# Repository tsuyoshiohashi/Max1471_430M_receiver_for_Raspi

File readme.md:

# MAX1471＋AD5700 430MHz AFSK receiver for Raspi

Receive 1200bps AFSK modulated waves in the 430Mhz band with RaspberryPi and an expansion board (MAX1471 + AD5700 430M radio hat, home made, see hat directory).
(In the photo, the LC series trap is directly attached to the U4 pin, but it has been modified in the circuit diagram.)

・The receiving frequency is fixed at the frequency determined by the XTAL frequency.

-Confirmed reception of a 1200bps AFSK signal in Asynchronous format (UART) sent by Gnuradio+Pluto. 

Please refer to the gnuradio directory for the transmitting program.

# Environment where operation has been confirmed
Raspi3B+　Raspberry Pi OS(bookworm)

You need to install pigpio.

# HAT configuration and operation
I use Analog Devices' MAX1471 for reception and AD5700 for AFSK demodulation.

MAX1471 operates in Continuous Receive Mode.

## receiving data
The received data RXD is connected to GPIO15 (pin10) of Raspi, and if the received data is in UART format, it can be treated as /dev/ttyAMA0 by setting UART on Raspi, and it can be displayed on minicom.
(Device name may vary depending on Raspino model)

`Example) $ cat /dev/ttyAMA0`

`Example) $ minicom -b 1200 -D /dev/ttyAMA0`

Since there is no squelch, the data becomes meaningless when there is no signal.

You can determine whether there is a received signal by looking at the CD signal of the AD5700 or by the size of the RSSI signal.

Please refer to rxafsk.py.

## receiving frequency
The receiving frequency is determined by the Xtal frequency using the following formula.
$$ frx = (fxtal * 32) + 10.7 (MHz) $$

13.2256MHz becomes 433.920MHz.

Although the data sheet says, the sensitivity is higher at frequencies slightly lower than this.
The prototype board had better sensitivity at frequencies several tens of KHz lower.

If you want to change the receiving frequency, you must also change the value of register 3 to fxtal/100kHz. (FREQ_XTAL in rxafskconst.py Please check the data sheet for details.)

# Software

The SPI of MAX1471 is controlled from the Raspi, but it is controlled by itself via GPIO, so there is no need to configure the SPI of the Raspi.
If SPI0 is enabled, please disable it. (Access as GPIO)

## rxafsk.py

If you run it from the command line as $ python rxafsk.py, it will perform the receiving operation.

Place regs.py, rxafskconst.py, and spi.py in the same directory.

When you run it, a prompt like "H>" will appear, allowing you to enter commands.

The prompt color is green when the synthesizer is locked, and red when it is not locked. (LOCKDET bit in Status Register)

When the LNA is High-gain, it is "H>", and when it is Low-gain, it is "L>".

A history function allows you to display and re-enter command history.

### Command
The following commands can be entered when the prompt is displayed.
### reset
Reset and initialize the MAX1471 and AD5700.

### rssi/r
Measures the received RSSI voltage and displays it in V units.

### cal/fskcal
Calibrate the FSK demodulator of MAX1471.

For some reason, sometimes (especially when receiving a weak signal?) when I perform calibration, the reception sensitivity and FSK signal output size change, and the signal that I was able to receive before can no longer be received (sensitivity worsens). The cause is unknown...
If you calibrate again, it will usually return to normal.

The data sheet says it is necessary if the voltage or temperature changes, but it may be better not to do this when reception is normal.

### read/rd n
Reads the contents of register number n (0-3,9) of MAX1471 and displays it in binary.

example:

H>read 0

Reg 0 = 11110110

### read/rd cd
Read the CD signal of AD5700.

### write/wr n data
Write data to register n of MAX1471. Enter data in hexadecimal.

example:

H>wr 0 f6

H>rd 0

Reg 0 = 11110110

===

Have A Fun!

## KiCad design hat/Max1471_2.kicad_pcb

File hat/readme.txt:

Edited with Kicad ver.7
It may not have been replicated properly.

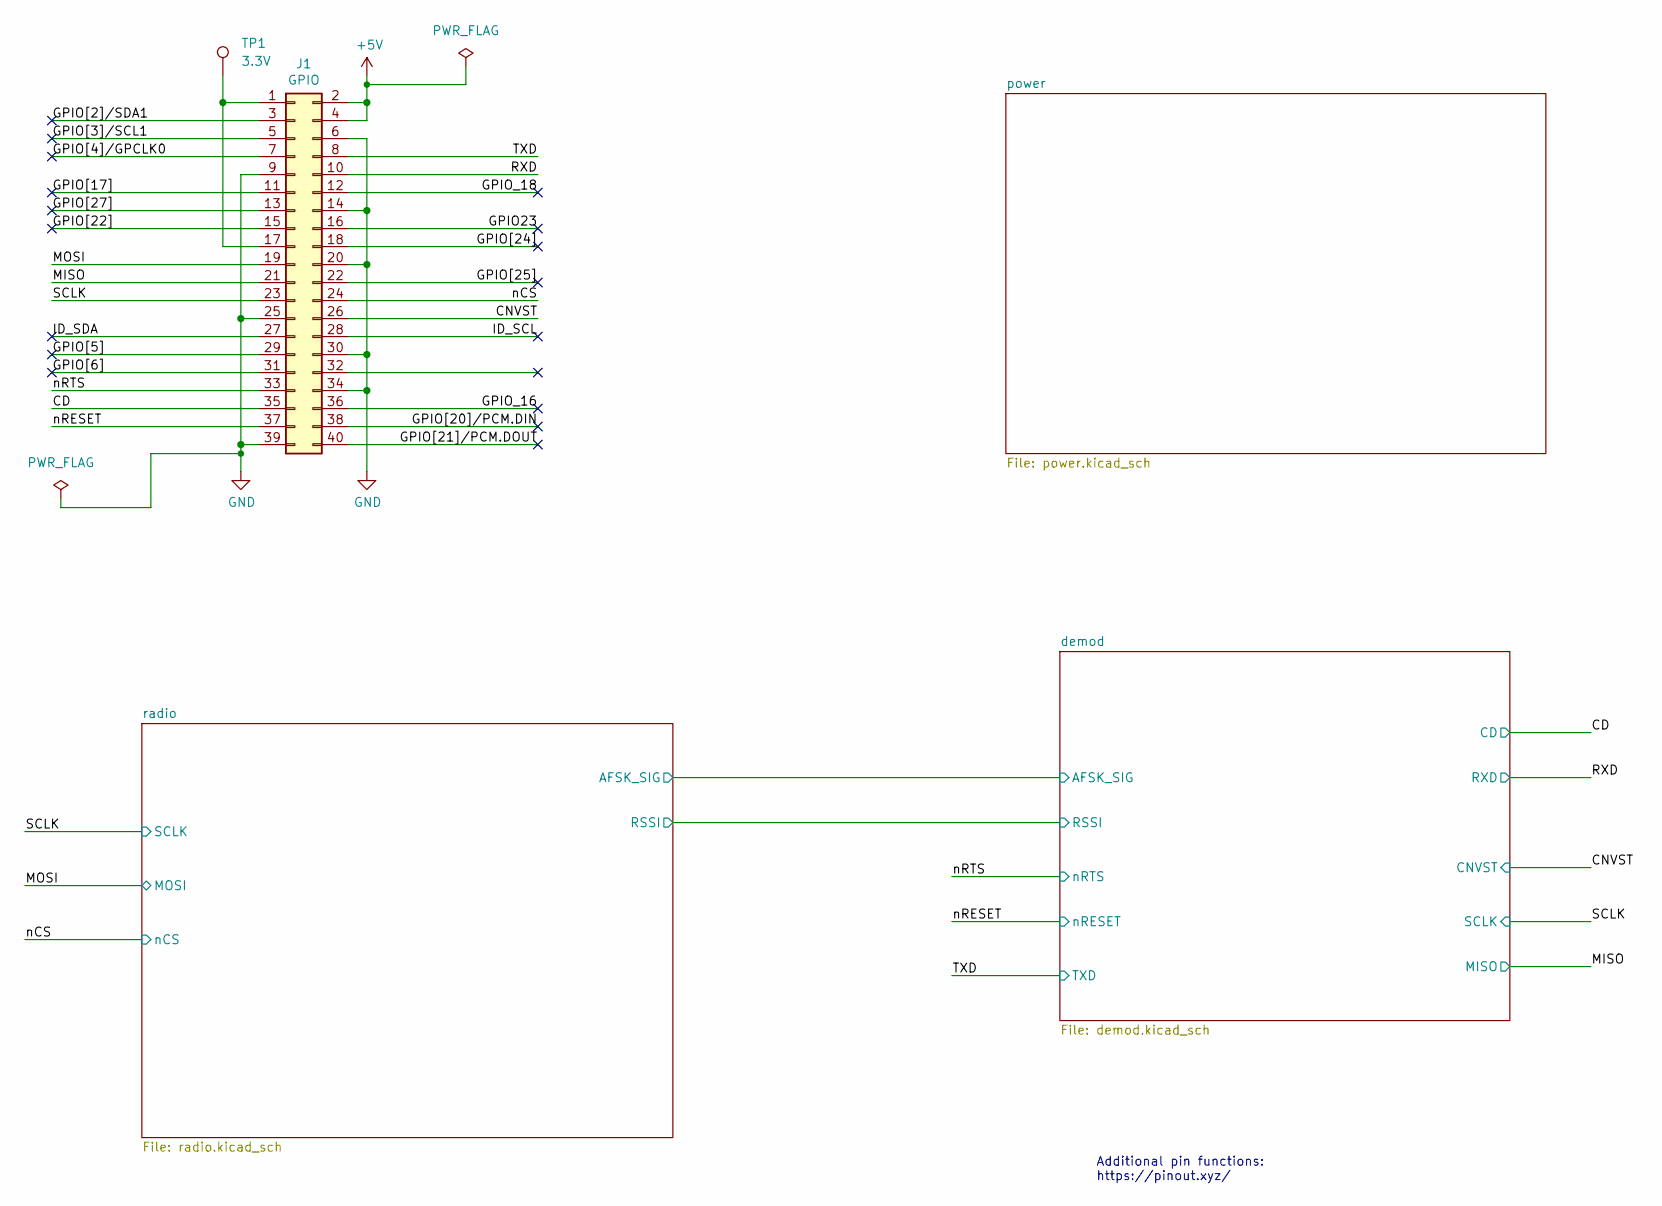
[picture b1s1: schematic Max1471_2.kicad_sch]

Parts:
J1: GPIO; PinSocket_2x20_P2.54mm_Vertical
TP1: 3.3V; TestPoint_Pad_D2.0mm

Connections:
+5V: J1.2, J1.4; also elsewhere on the board
/CD: J1.35; also elsewhere on the board
/CNVST: J1.26; also elsewhere on the board
/GPIO23: J1.16
/GPIO[2]/SDA1: J1.3
/GPIO[3]/SCL1: J1.5
/GPIO[4]/GPCLK0: J1.7
/GPIO[5]: J1.29
/GPIO[6]: J1.31
/GPIO[17]: J1.11
/GPIO[20]/PCM.DIN: J1.38
/GPIO[21]/PCM.DOUT: J1.40
/GPIO[22]: J1.15
/GPIO[24]: J1.18
/GPIO[25]: J1.22
/GPIO[27]: J1.13
/GPIO_16: J1.36
/GPIO_18: J1.12
/ID_SCL: J1.28
/ID_SDA: J1.27
/MISO: J1.21; also elsewhere on the board
/MOSI: J1.19; also elsewhere on the board
/RXD: J1.10; also elsewhere on the board
/SCLK: J1.23; also elsewhere on the board
/TXD: J1.8; also elsewhere on the board
/nCS: J1.24; also elsewhere on the board
/nRESET: J1.37; also elsewhere on the board
/nRTS: J1.33; also elsewhere on the board
GND: J1.6, J1.9, J1.14, J1.20, J1.25, J1.30, J1.34, J1.39; also elsewhere on the board
unnamed: J1.1, J1.17, TP1.1

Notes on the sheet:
Additional pin functions: https://pinout.xyz/

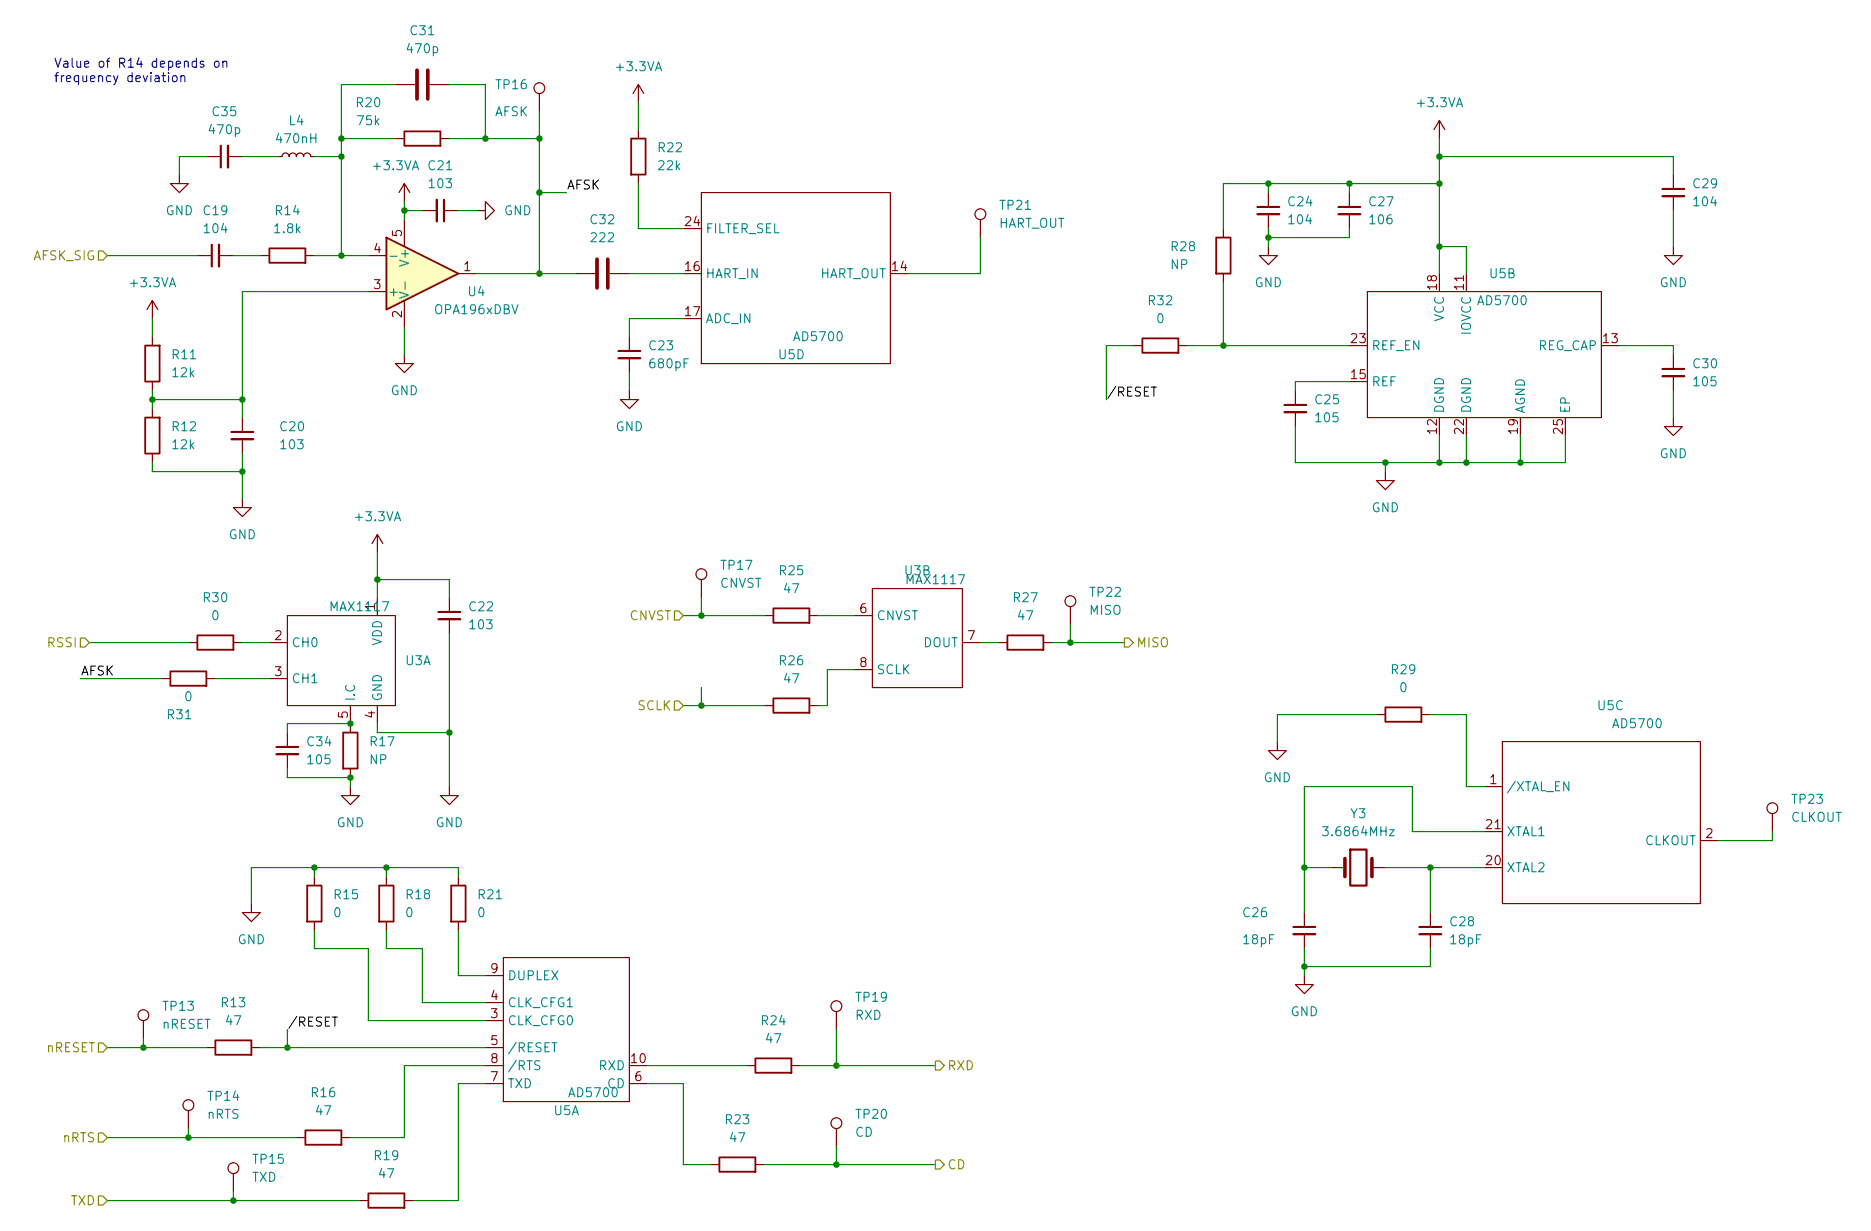
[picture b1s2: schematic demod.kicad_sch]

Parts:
C19, C24, C29: 104; C_0603_1608Metric_Pad1.08x0.95mm_HandSolder
C20, C21, C22: 103; C_0603_1608Metric_Pad1.08x0.95mm_HandSolder
C23: 680pF; C_0603_1608Metric_Pad1.08x0.95mm_HandSolder
C25, C30, C34: 105; C_0603_1608Metric_Pad1.08x0.95mm_HandSolder
C26, C28: 18pF; C_0603_1608Metric_Pad1.08x0.95mm_HandSolder
C27: 106; C_0603_1608Metric_Pad1.08x0.95mm_HandSolder
C31, C35: 470p; C_0603_1608Metric_Pad1.08x0.95mm_HandSolder
C32: 222; C_0603_1608Metric_Pad1.08x0.95mm_HandSolder
L4: 470nH; L_0603_1608Metric_Pad1.05x0.95mm_HandSolder
R11, R12: 12k; R_0603_1608Metric_Pad0.98x0.95mm_HandSolder
R13, R16, R19, R23, R24, R25, R26, R27: 47; R_0603_1608Metric_Pad0.98x0.95mm_HandSolder
R14: 1.8k; R_0603_1608Metric_Pad0.98x0.95mm_HandSolder
R15, R18, R21, R29, R30, R31, R32: 0; R_0603_1608Metric_Pad0.98x0.95mm_HandSolder
R17, R28: NP; R_0603_1608Metric_Pad0.98x0.95mm_HandSolder
R20: 75k; R_0603_1608Metric_Pad0.98x0.95mm_HandSolder
R22: 22k; R_0603_1608Metric_Pad0.98x0.95mm_HandSolder
TP13: nRESET; TestPoint_Pad_D2.0mm
TP14: nRTS; TestPoint_Pad_D2.0mm
TP15: TXD; TestPoint_Pad_D2.0mm
TP16: AFSK; TestPoint_Pad_D2.0mm
TP17: CNVST; TestPoint_Pad_D2.0mm
TP19: RXD; TestPoint_Pad_D2.0mm
TP20: CD; TestPoint_Pad_D2.0mm
TP21: HART_OUT; TestPoint_Pad_D2.0mm
TP22: MISO; TestPoint_Pad_D2.0mm
TP23: CLKOUT; TestPoint_Pad_D2.0mm
U3: MAX1117; SOT-23-8
U4: OPA196xDBV; SOT-23-5
U5: AD5700; QFN-24-1EP_4x4mm_P0.5mm_EP2.15x2.15mm
Y3: 3.6864MHz; Crystal_SMD_HC49-SD

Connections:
+3.3VA: C21.2, C22.1, C24.1, C27.1, C29.1, R11.2, R22.1, R28.1, U3.1 (VDD), U4.5 (V+), U5.11 (IOVCC), U5.18 (VCC); also elsewhere on the board
/CD: R23.2, TP20.1; also elsewhere on the board
/CNVST: R25.1, TP17.1; also elsewhere on the board
/MISO: R27.2, TP22.1; also elsewhere on the board
/RXD: R24.2, TP19.1; also elsewhere on the board
/SCLK: R26.1; also elsewhere on the board
/TXD: R19.1, TP15.1; also elsewhere on the board
/demod/AFSK: C31.2, C32.1, R20.2, R31.1, TP16.1, U4.1
/demod/AFSK_SIG: C19.1; also elsewhere on the board
/demod/RSSI: R30.1; also elsewhere on the board
/demod//RESET: R13.2, R32.1, U5.5 (/RESET)
/nRESET: R13.1, TP13.1; also elsewhere on the board
/nRTS: R16.1, TP14.1; also elsewhere on the board
GND: C20.2, C21.1, C22.2, C23.2, C24.2, C25.2, C26.2, C27.2, C28.2, C29.2, C30.2, C34.2, C35.1, R12.1, R15.1, R17.2, R18.1, R21.1, R29.1, U3.4 (GND), U4.2 (V-), U5.12 (DGND), U5.19 (AGND), U5.22 (DGND), U5.25 (EP); also elsewhere on the board
unnamed: C19.2, R14.1
unnamed: C35.2, L4.1
unnamed: R30.2, U3.2 (CH0)
unnamed: R31.2, U3.3 (CH1)
unnamed: C34.1, R17.1, U3.5 (I.C)
unnamed: R25.2, U3.6 (CNVST)
unnamed: R27.1, U3.7 (DOUT)
unnamed: R26.2, U3.8 (SCLK)
unnamed: C20.1, R11.1, R12.2, U4.3 (+)
unnamed: C31.1, L4.2, R14.2, R20.1, U4.4 (-)
unnamed: R23.1, U5.6 (CD)
unnamed: R15.2, U5.3 (CLK_CFG0)
unnamed: R18.2, U5.4 (CLK_CFG1)
unnamed: R21.2, U5.9 (DUPLEX)
unnamed: R24.1, U5.10 (RXD)
unnamed: R19.2, U5.7 (TXD)
unnamed: R16.2, U5.8 (/RTS)
unnamed: C25.1, U5.15 (REF)
unnamed: R28.2, R32.2, U5.23 (REF_EN)
unnamed: C30.1, U5.13 (REG_CAP)
unnamed: TP23.1, U5.2 (CLKOUT)
unnamed: C26.1, U5.21 (XTAL1), Y3.1
unnamed: C28.1, U5.20 (XTAL2), Y3.2
unnamed: R29.2, U5.1 (/XTAL_EN)
unnamed: C23.1, U5.17 (ADC_IN)
unnamed: R22.2, U5.24 (FILTER_SEL)
unnamed: C32.2, U5.16 (HART_IN)
unnamed: TP21.1, U5.14 (HART_OUT)

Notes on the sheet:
Value of R14 depends on frequency deviation

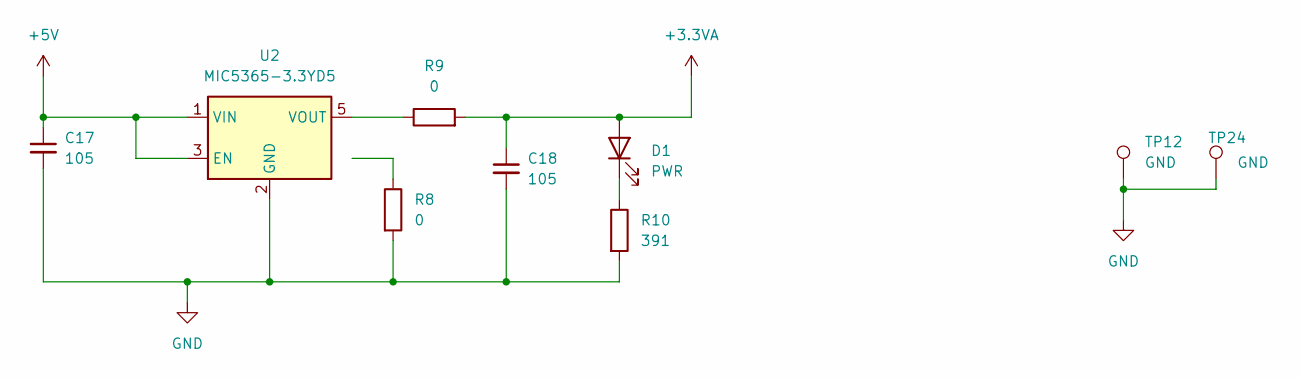
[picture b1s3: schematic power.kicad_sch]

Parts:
C17, C18: 105; C_0603_1608Metric_Pad1.08x0.95mm_HandSolder
D1: PWR; LED_0603_1608Metric_Pad1.05x0.95mm_HandSolder
R8, R9: 0; R_0603_1608Metric_Pad0.98x0.95mm_HandSolder
R10: 391; R_0603_1608Metric_Pad0.98x0.95mm_HandSolder
TP12, TP24: GND; TestPoint_Pad_D2.0mm
U2: MIC5365-3.3YD5; SOT-23-5

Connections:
+3.3VA: C18.1, D1.2 (A), R9.2; also elsewhere on the board
+5V: C17.1, U2.1 (VIN), U2.3 (EN); also elsewhere on the board
GND: C17.2, C18.2, R8.2, R10.2, TP12.1, TP24.1, U2.2 (GND); also elsewhere on the board
unnamed: D1.1 (K), R10.1
unnamed: R8.1, U2.4 (NC)
unnamed: R9.1, U2.5 (VOUT)

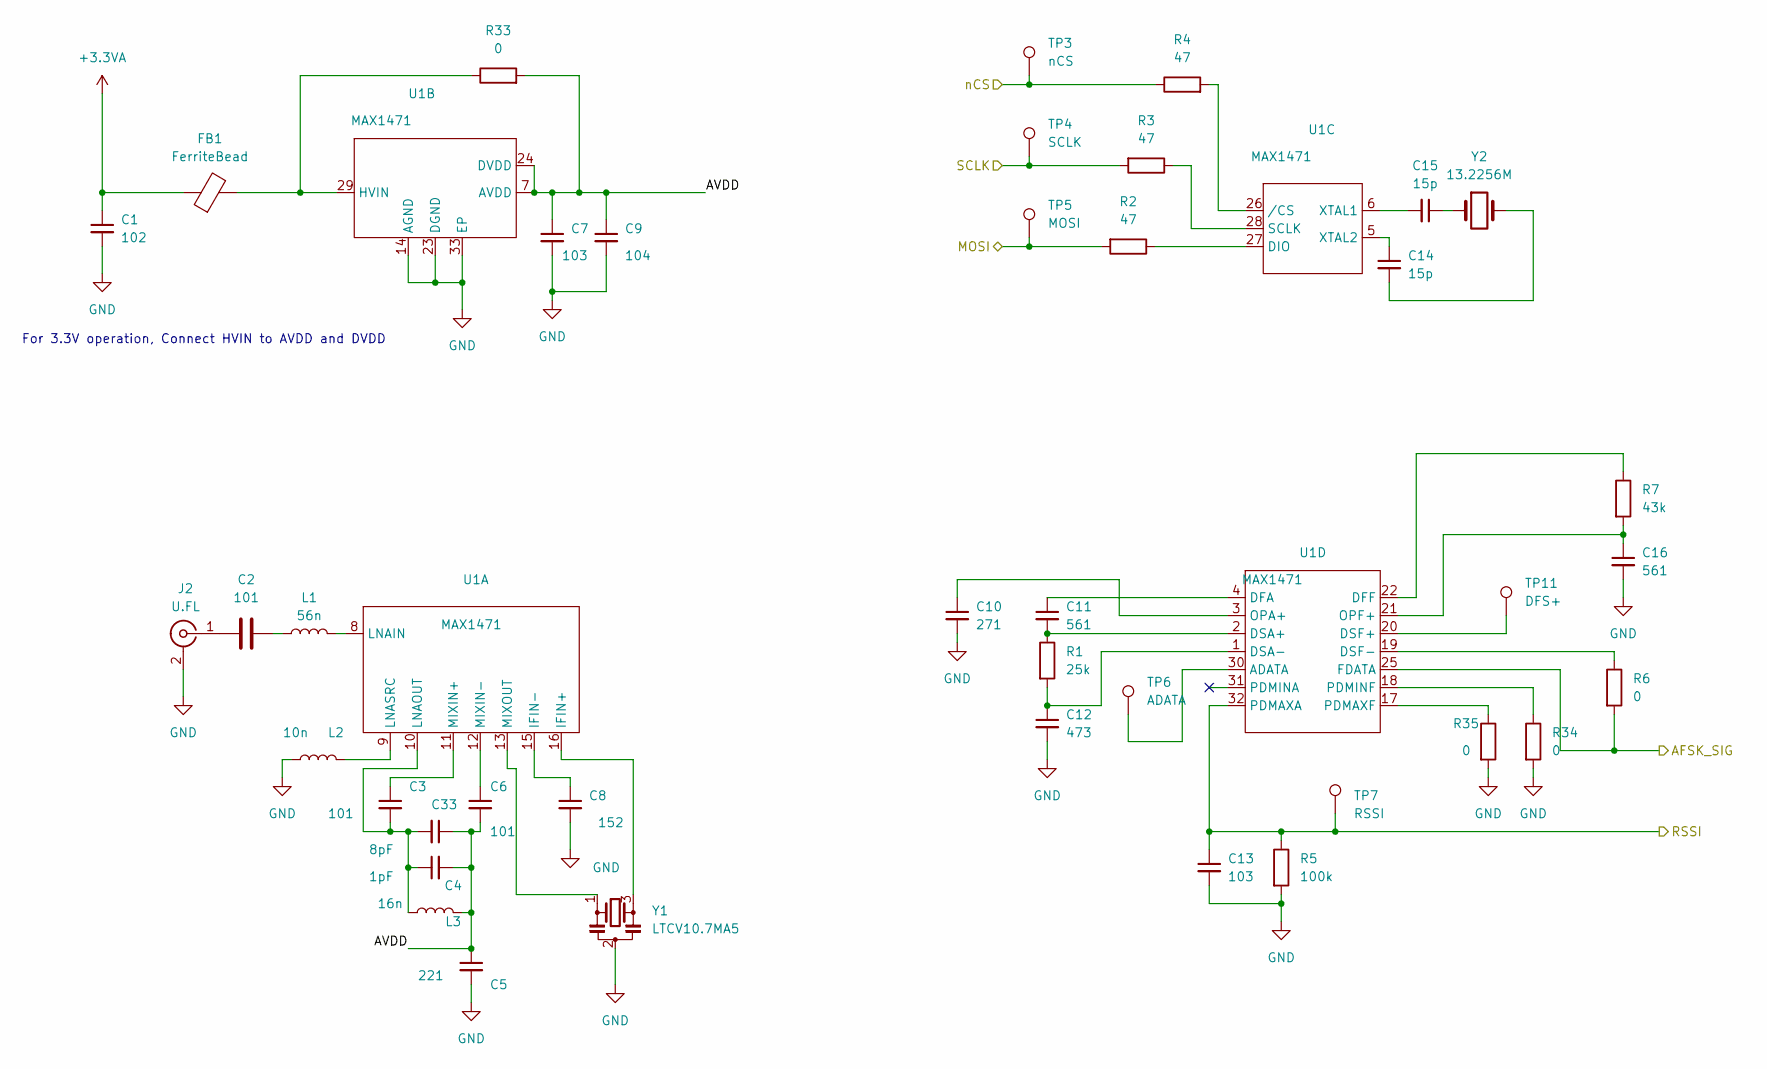
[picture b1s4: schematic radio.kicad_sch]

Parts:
C1: 102; C_0603_1608Metric_Pad1.08x0.95mm_HandSolder
C2, C3, C6: 101; C_0603_1608Metric_Pad1.08x0.95mm_HandSolder
C4: 1pF; C_0603_1608Metric_Pad1.08x0.95mm_HandSolder
C5: 221; C_0603_1608Metric_Pad1.08x0.95mm_HandSolder
C7, C13: 103; C_0603_1608Metric_Pad1.08x0.95mm_HandSolder
C8: 152; C_0603_1608Metric_Pad1.08x0.95mm_HandSolder
C9: 104; C_0603_1608Metric_Pad1.08x0.95mm_HandSolder
C10: 271; C_0603_1608Metric_Pad1.08x0.95mm_HandSolder
C11, C16: 561; C_0603_1608Metric_Pad1.08x0.95mm_HandSolder
C12: 473; C_0603_1608Metric_Pad1.08x0.95mm_HandSolder
C14, C15: 15p; C_0603_1608Metric_Pad1.08x0.95mm_HandSolder
C33: 8pF; C_0603_1608Metric_Pad1.08x0.95mm_HandSolder
FB1: FerriteBead; L_0603_1608Metric_Pad1.05x0.95mm_HandSolder
J2: U.FL; U.FL_Hirose_U.FL-R-SMT-1_Vertical
L1: 56n; L_0603_1608Metric_Pad1.05x0.95mm_HandSolder
L2: 10n; L_0603_1608Metric_Pad1.05x0.95mm_HandSolder
L3: 16n; L_0603_1608Metric_Pad1.05x0.95mm_HandSolder
R1: 25k; R_0603_1608Metric_Pad0.98x0.95mm_HandSolder
R2, R3, R4: 47; R_0603_1608Metric_Pad0.98x0.95mm_HandSolder
R5: 100k; R_0603_1608Metric_Pad0.98x0.95mm_HandSolder
R6, R33, R34, R35: 0; R_0603_1608Metric_Pad0.98x0.95mm_HandSolder
R7: 43k; R_0603_1608Metric_Pad0.98x0.95mm_HandSolder
TP3: nCS; TestPoint_Pad_D2.0mm
TP4: SCLK; TestPoint_Pad_D2.0mm
TP5: MOSI; TestPoint_Pad_D2.0mm
TP6: ADATA; TestPoint_Pad_D2.0mm
TP7: RSSI; TestPoint_Pad_D2.0mm
TP11: DFS+; TestPoint_Pad_D2.0mm
U1: MAX1471; QFN-32-1EP_5x5mm_P0.5mm_EP3.1x3.1mm
Y1: LTCV10.7MA5; LTCV10.7M
Y2: 13.2256M; Crystal_SMD_HC49-SD

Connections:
+3.3VA: C1.1, FB1.1; also elsewhere on the board
/MOSI: R2.2, TP5.1; also elsewhere on the board
/SCLK: R3.2, TP4.1; also elsewhere on the board
/demod/AFSK_SIG: R6.2, U1.25 (FDATA); also elsewhere on the board
/demod/RSSI: C13.1, R5.1, TP7.1, U1.32 (PDMAXA); also elsewhere on the board
/nCS: R4.1, TP3.1; also elsewhere on the board
/radio/AVDD: C4.2, C5.1, C6.2, C7.1, C9.1, C33.1, L3.2, R33.2, U1.7 (AVDD), U1.24 (DVDD)
GND: C1.2, C5.2, C7.2, C8.2, C9.2, C10.2, C12.2, C13.2, C16.2, J2.2 (Ext), L2.2, R5.2, R34.2, R35.2, U1.14 (AGND), U1.23 (DGND), U1.33 (EP), Y1.2; also elsewhere on the board
unnamed: C2.2, L1.1
unnamed: C14.2, Y2.2
unnamed: C15.1, Y2.1
unnamed: C2.1, J2.1 (In)
unnamed: U1.16 (IFIN+), Y1.3
unnamed: C8.1, U1.15 (IFIN-)
unnamed: L1.2, U1.8 (LNAIN)
unnamed: C3.2, C4.1, C33.2, L3.1, U1.10 (LNAOUT)
unnamed: L2.1, U1.9 (LNASRC)
unnamed: C3.1, U1.11 (MIXIN+)
unnamed: C6.1, U1.12 (MIXIN-)
unnamed: U1.13 (MIXOUT), Y1.1
unnamed: FB1.2, R33.1, U1.29 (HVIN)
unnamed: R2.1, U1.27 (DIO)
unnamed: R3.1, U1.28 (SCLK)
unnamed: C15.2, U1.6 (XTAL1)
unnamed: C14.1, U1.5 (XTAL2)
unnamed: R4.2, U1.26 (/CS)
unnamed: TP6.1, U1.30 (ADATA)
unnamed: C11.1, U1.4 (DFA)
unnamed: R7.1, U1.22 (DFF)
unnamed: C11.2, R1.1, U1.2 (DSA+)
unnamed: C12.1, R1.2, U1.1 (DSA-)
unnamed: TP11.1, U1.20 (DSF+)
unnamed: R6.1, U1.19 (DSF-)
unnamed: C10.1, U1.3 (OPA+)
unnamed: C16.1, R7.2, U1.21 (OPF+)
unnamed: R35.1, U1.17 (PDMAXF)
unnamed: R34.1, U1.18 (PDMINF)

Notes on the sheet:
For 3.3V operation, Connect HVIN to AVDD and DVDD

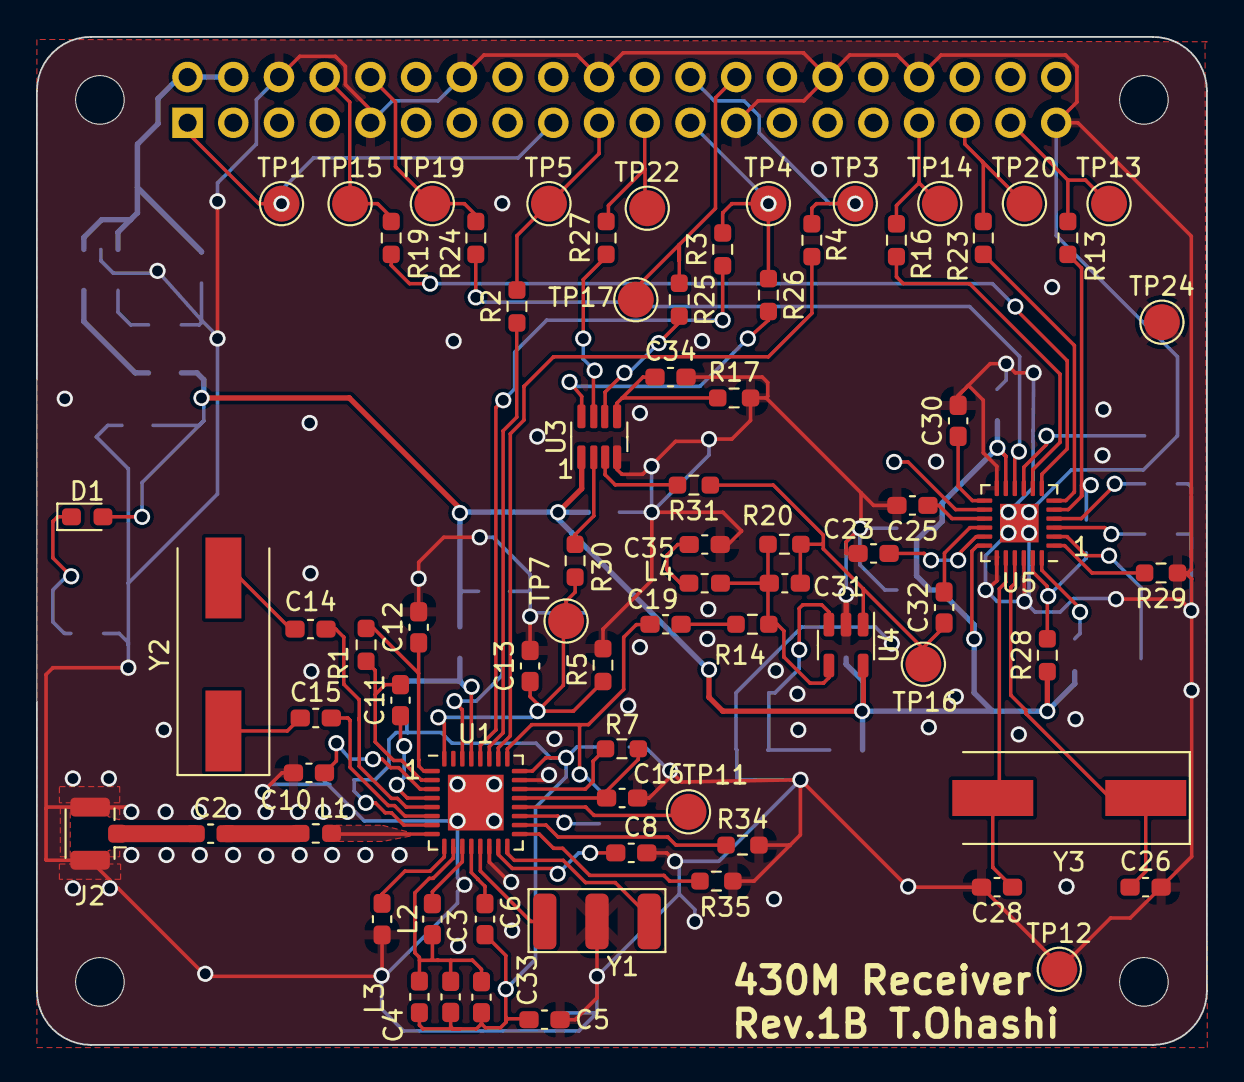
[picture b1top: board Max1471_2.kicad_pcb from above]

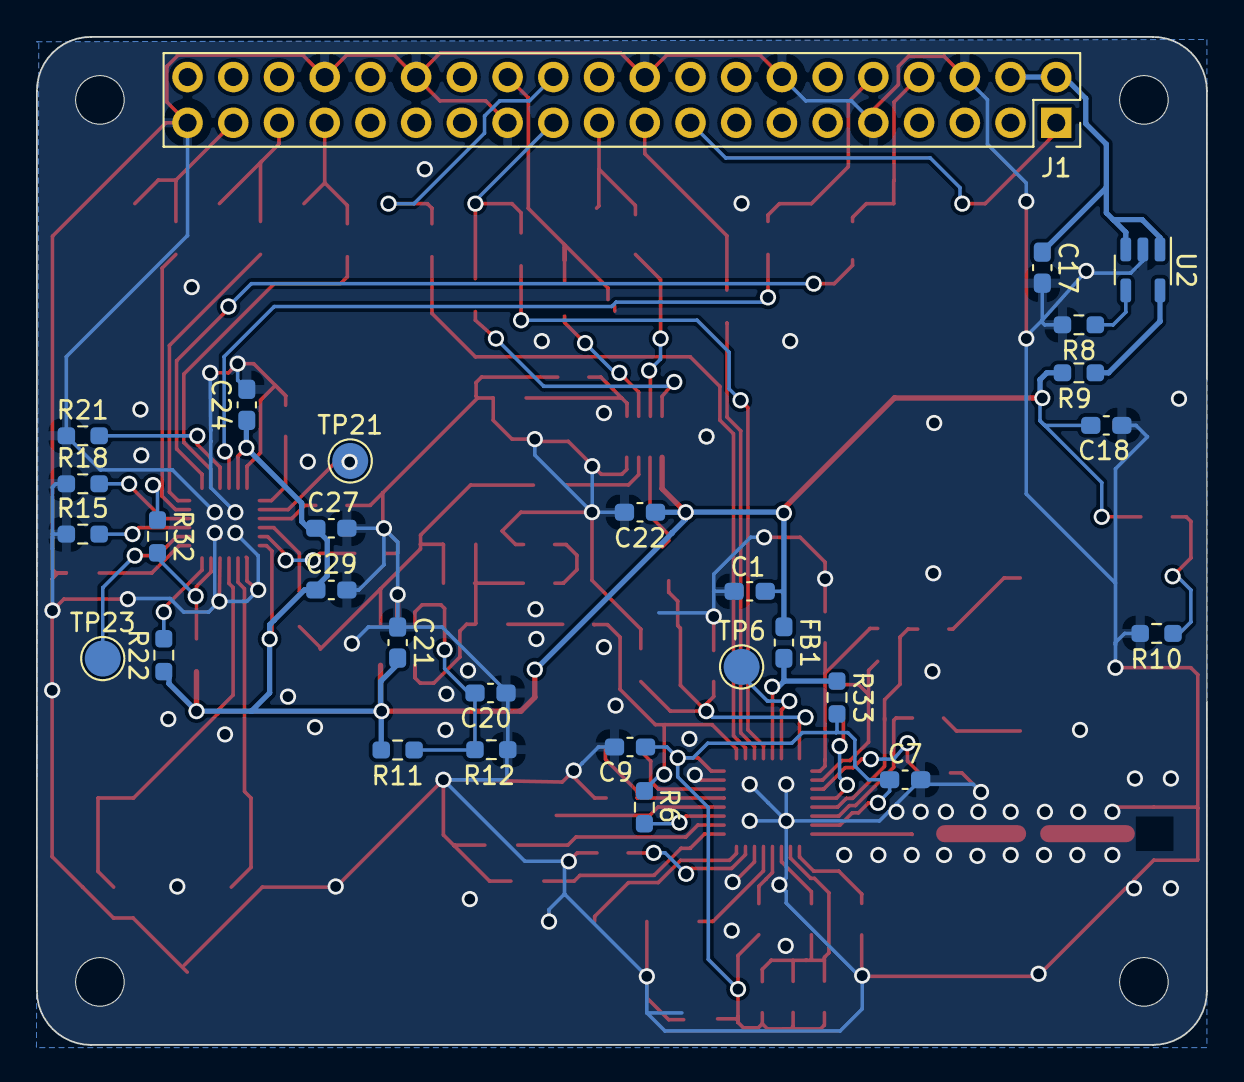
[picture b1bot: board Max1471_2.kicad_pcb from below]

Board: 2 copper layers, 65.0 x 56.0 mm, 109 parts (29 on the bottom side), 79 nets.

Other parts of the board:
MH1, MH2, MH3, MH4: MountingHole_2.7mm_M2.5

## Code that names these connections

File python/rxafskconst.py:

#
# rxafskconst.py
# parameters for regs.py, spi.py and rxafsk.py 

# This implementation is for personal experiments.
# Copyright (c) 2024 Tsuyoshi Ohashi
# Released under the MIT license
# https://opensource.org/licenses/mit-license.php

# GPIO pin config
# device_name - BCM# - raspi_IO_pin#
# SoftSPI (NOT BCM system SPI)
GPIO_nCS = 8   # GPIO8 = pin24
GPIO_MOSI = 10    # GPIO10 = pin19  # max1471 Bi-directional

GPIO_MISO = 9    # GPIO9 = pin21    # max1117(ADC)
GPIO_SCLK = 11   # GPIO11 = pin23

GPIO_nRTS = 13  # GPIO13 = pin33
GPIO_nRESET = 26 # GPIO26 = pin37
GPIO_CD = 19 # GPIO19 = pin35
TXD = 8 #  
RXD = 10 # 

#max1117
# down edge starts convert
# 1 edge for CH0, 2 edgs for CH1
GPIO_CNVST = 7 # GPIO7 = pin26
 
#GPIO1 = 6   # GPIO6 = pin31
#GPIO2 = 27  # GPIO27 = pin13
#GPIO3 = 17  # GPIO17 = pin11
#GPIOSDN = 4 # GPIO4 = pin7
#GPIOnIRQ = 5   # GPIO05 = pin29

# Config GPIO
#GPIO_TX_DATA = GPIO0 
#GPIO_CTS = GPIO1
#GPIO_SHDN = GPIOSDN

# Commands for max1471
CMD_NOP = 0x0
CMD_WRITE = 0x1
CMD_READ = 0x2
CMD_RESET = 0x3

# Registers in max1471
REG_PWR_CFG = 0x0
REG_CONFIG = 0x1
REG_CONTROL = 0x2
REG_OSC_FREQ = 0x3
REG_STATUS = 0x9
REG_AGC_DWELL = 0xA

# XTAL
FREQ_XTAL = 0x84  # 13.2256MHz/100kHz=132=0x84 

###

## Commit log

2024-04-12 add readme.txt
2024-04-12 edit readme.*
